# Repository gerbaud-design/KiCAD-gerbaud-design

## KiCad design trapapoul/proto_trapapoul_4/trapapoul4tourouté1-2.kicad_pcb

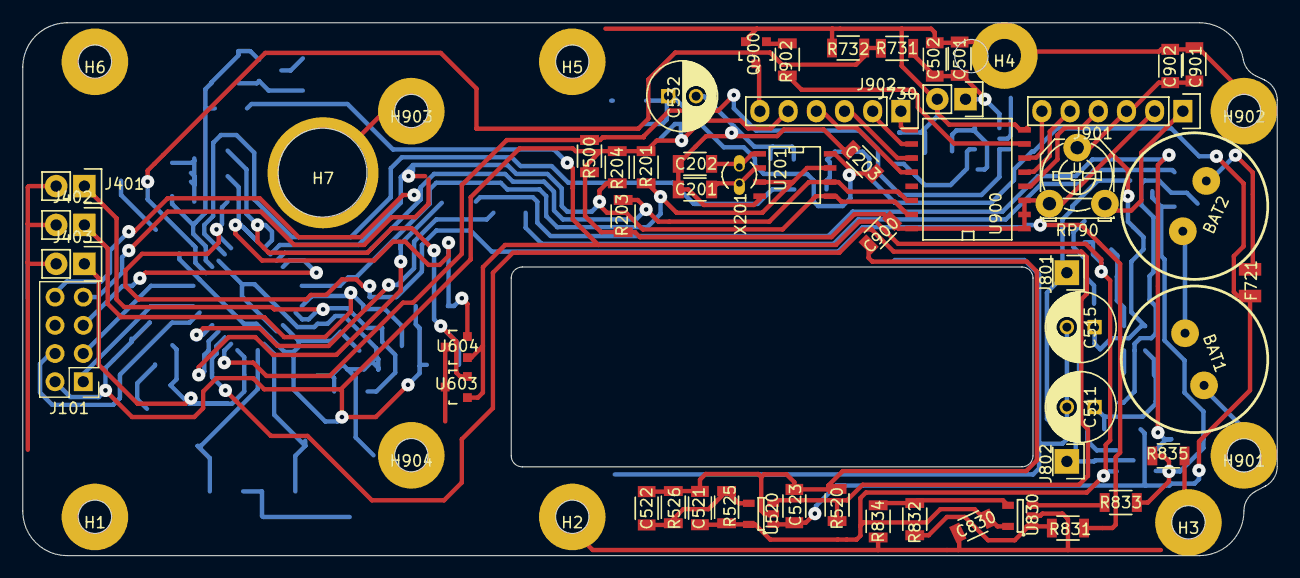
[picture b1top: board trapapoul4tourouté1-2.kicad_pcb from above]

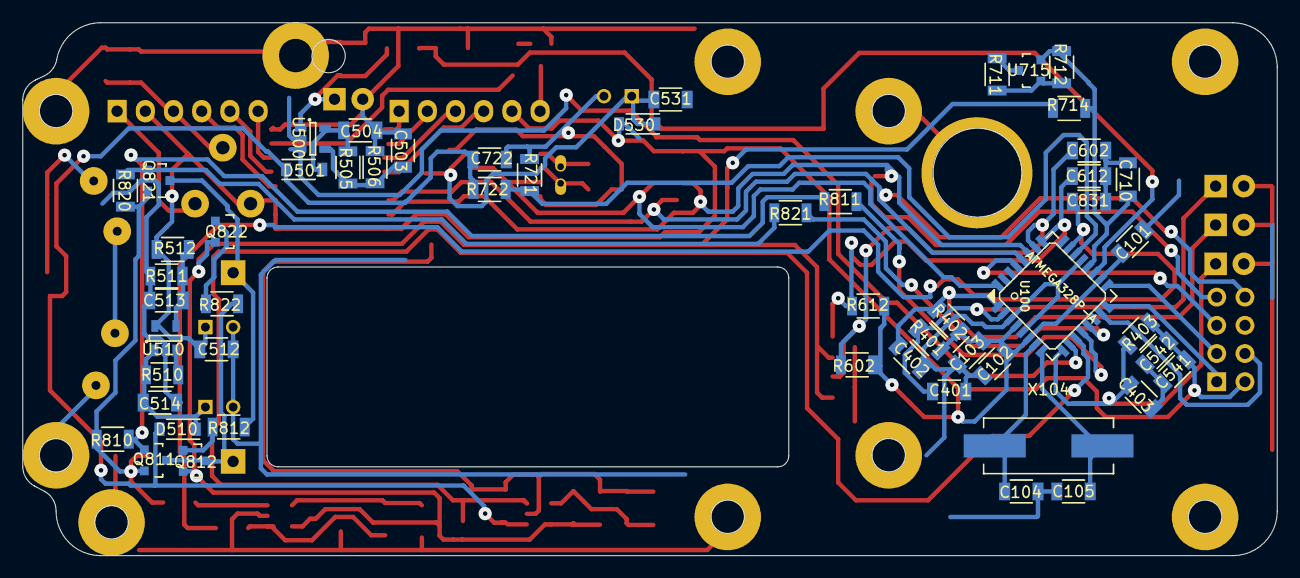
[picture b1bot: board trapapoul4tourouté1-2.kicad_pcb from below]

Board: 2 copper layers, 113.0 x 48.0 mm, 116 parts (54 on the bottom side), 60 nets.

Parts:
BAT1, BAT2: BAT; HFC1330
C101, C103, C203, C401, C402, C403, C502, C541, C710: 10n; C_1206
C102, C830, C831: 100n; C_1206
C104, C105, C201, C202: 10p; C_1206
C501, C504, C512, C514, C521, C523, C531, C722, C902: 10uF; C_1206
C503, C513, C522: 470p; C_1206
C511, C515, C532: 470uF; C_Radial_D6.3_L11.2_P2.5
C542, C602, C612, C900: 100nF; C_1206
C901: 10nF; C_1206
D501, D510, D530: SCHOTTKY; SOD-123
F721: 5A; Fuse_SMD1206_Reflow
H1, H2, H3, H4, H5, H6, H901, H902, H903, H904: hole; 3mm_screw
H7: hole; MF85
J101: HEADER_4x2; Pin_Header_Straight_2x04_Pitch2.54mm
J401, J402, J403, J730: HEADER_2; Pin_Header_Straight_1x02
J801, J802: HEADER_1; Pin_Header_Straight_1x01
J901, J902: HEADER_6; Pin_Header_Straight_1x06
Q811, Q821, Q900: PBSS4320; SOT-23
Q812, Q822: PBSS5350; SOT-23
R201, R401, R402, R403, R500, R510, R520, R711, R714, R722, R731, R832: 10k; R_1206
R203, R204, R732: 2.2k; R_1206
R505, R506, R525, R526: tbd; R_1206
R511: 100k; R_1206
R512: 33k; R_1206
R602, R612: 4k7; R_1206
R712, R721, R902: 4.7k; R_1206
R810, R820: 3k3; R_1206
R811, R812, R821, R822: 330; R_1206
R831, R833, R834: 1k; R_1206
R835: 0R2; R_1206
RP90: 100k; Potentiometer_Triwood_RM-065
U100: ATMEGA328P-A; lqfp32
U201: MCP7940; SOIC-8-N
U500, U510, U520: MIC5205; SOT-23-5
U603, U604: A3144; SOT-23
U715: TLV431-DBZ; SOT-23
U830: MCP601-SOT; SOT-23-5
U900: PCF8574; SO-16-W
X104: 16M; Crystal_HC49-SD_SMD
X201: 32.768K; Crystal_Round_Vertical_3mm_BigPad

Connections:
BP1: C401.1, J401.1, R401.2, U100.2
BP2: C402.1, J402.1, R402.2, U100.1
BP3: C403.1, J403.1, R403.2, U100.9
C_bkw: R821.1, U100.13
C_frw: R811.2, U100.12
GND: BAT1.2, C101.1, C102.1, C103.1, C104.1, C105.1, C201.2, C202.2, C203.2, C401.2, C402.2, C403.2, C501.2, C502.2, C503.2, C504.2, C511.2, C512.2, C513.2, C514.2, C515.2, C521.2, C522.2, C523.2, C531.2, C532.2, C541.2, C542.2, C602.2, C612.1, C710.2, C722.2, C830.2, C831.2, C900.2, C901.1, C902.1, H1.1, H2.1, H3.1, H4.1, H5.1, H6.1, H7.1, H901.1, H902.1, H903.1, H904.1, J101.6, J401.2, J402.2, J403.2, J730.2, J901.1, Q900.2, R506.2, R511.1, R520.1, R526.1, R711.2, R721.1, R732.2, R834.2, R835.1, RP90.3, U100.3, U100.5, U100.21, U201.4, U500.2, U510.2, U520.2, U603.3, U604.3, U715.3, U830.2, U900.8
M_bat: R721.2, R722.2, U100.22
M_imot: C831.1, R831.1, U100.23
M_sol: R731.1, R732.1, U100.19
unnamed: BAT1.1, BAT2.2
unnamed: BAT2.1, F721.1
unnamed: C104.2, U100.7, X104.1
unnamed: C105.2, U100.8, X104.2
unnamed: C201.1, U201.2, X201.2
unnamed: C202.1, U201.1, X201.1
unnamed: C503.1, R505.2, R506.1, U500.4
unnamed: C504.1, D501.2, R505.1, U500.5
unnamed: C511.1, C514.1, D510.1, R510.1, U510.1
unnamed: C513.1, R511.2, R512.1, U510.4
unnamed: C522.1, R525.1, R526.2, U520.4
unnamed: C901.2, C902.2, J901.3, RP90.2
unnamed: J101.1, U100.16
unnamed: J101.3, U100.17
unnamed: J101.4, U100.15
unnamed: J101.5, U100.29
unnamed: J801.1, Q821.3, Q822.3, R812.1
unnamed: J802.1, Q811.3, Q812.3, R822.1
unnamed: J901.4, U900.4
unnamed: J901.5, U900.5
unnamed: J901.6, U900.6
unnamed: J902.1, U900.9
unnamed: J902.2, U900.10
unnamed: J902.3, U900.11
unnamed: J902.4, U900.12
unnamed: J902.6, Q900.3
unnamed: Q811.1, R810.2, R811.1
unnamed: Q811.2, Q821.2, R810.1, R820.1, R833.2, R835.2
unnamed: Q812.1, R812.2
unnamed: Q821.1, R820.2, R821.2
unnamed: Q822.1, R822.2
unnamed: Q900.1, R902.2
unnamed: R510.2, U510.3
unnamed: R711.1, R712.2, U715.1
unnamed: R831.2, R832.1, U830.1
unnamed: R832.2, R834.1, U830.4
unnamed: R833.1, U830.3
unnamed: R902.1, U900.7
SCL: J101.8, R203.2, U100.28, U201.6, U900.14
SDA: J101.7, R204.2, U100.27, U201.5, U900.15
VCC: C101.2, C102.2, C103.2, C512.1, C515.1, C541.1, C542.1, C900.1, D530.2, J101.2, J901.2, J902.5, R201.1, R203.1, R204.1, R401.1, R402.1, R403.1, R500.1, R512.2, R602.2, R612.1, RP90.1, U100.4, U100.6, U100.18, U510.5, U900.1, U900.2, U900.3, U900.16
VPP: C521.1, C830.1, Q812.2, Q822.2, R525.2, R714.1, U520.5, U603.1, U604.1, U830.5
V_bat: C523.1, C722.1, D501.1, D510.2, F721.2, R722.1, U520.1
V_ref: C710.1, R712.1, R714.2, U100.20, U715.2
V_rtc: C203.1, C531.1, C532.1, D530.1, U201.8
V_sol: C501.1, C502.1, J730.1, R731.2, U500.1
VppEn: R520.2, U100.11, U520.3
alarm: R201.2, U100.32, U201.3, U201.7
charge_OFF: R500.2, U100.10, U500.3
quadA: C602.1, R602.1, U100.26, U603.2
quadB: C612.2, R612.2, U100.25, U604.2

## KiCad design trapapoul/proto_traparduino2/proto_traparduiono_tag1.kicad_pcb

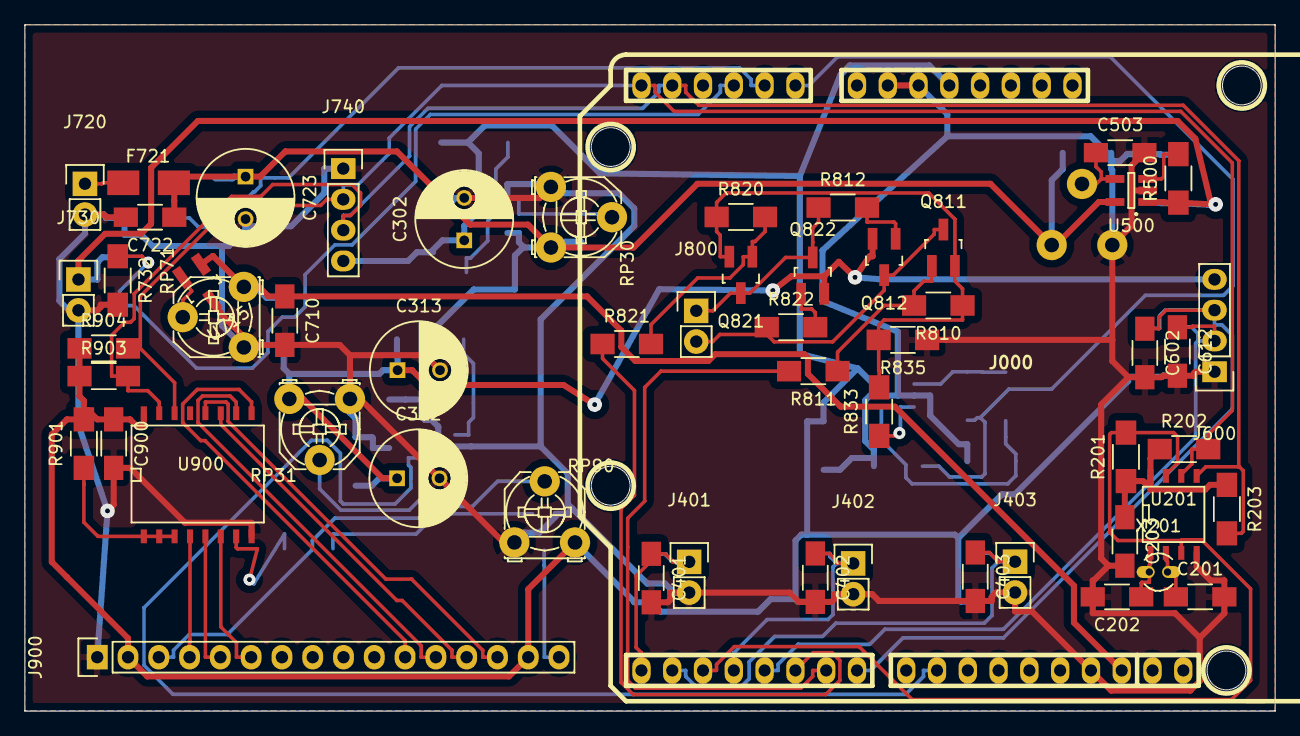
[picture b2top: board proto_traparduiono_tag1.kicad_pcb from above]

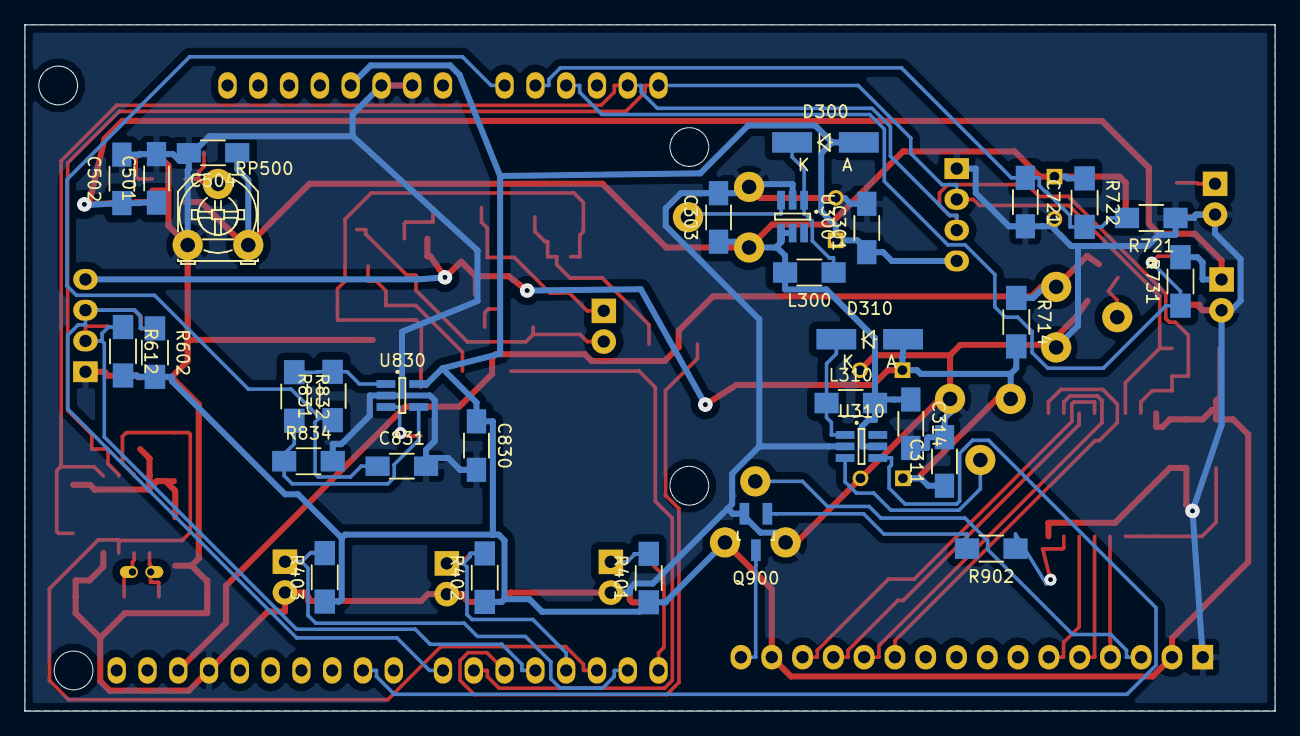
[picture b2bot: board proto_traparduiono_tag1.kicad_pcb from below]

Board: 2 copper layers, 103.1 x 56.6 mm, 88 parts (32 on the bottom side), 53 nets.

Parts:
C201, C202: 10p; C_1206_HandSoldering
C203, C401, C402, C403, C502, C503, C710, C721: 10n; C_1206_HandSoldering
C301, C303, C311, C314, C501, C504, C722: 10uF; C_1206_HandSoldering
C302, C312, C313, C723: 470uF; C_Radial_D8_L11.5_P3.5
C602, C612, C900: 100nF; C_1206_HandSoldering
C830, C831: 100n; C_1206_HandSoldering
D300, D310: SCHOTTKY; MiniMELF_Handsoldering
F721: 5A; Fuse_SMD1206_HandSoldering
J000: Arduino_Header; arduino_header
J401, J402, J403, J720, J730, J800: HEADER_2; Pin_Header_Straight_1x02
J600, J740: HEADER_4; Pin_Header_Straight_1x04
J900: HEADER_16; Pin_Header_Straight_1x16
L300, L310: INDUCTOR; R_1206_HandSoldering
Q811, Q821, Q900: PBSS4320; SOT-23_Handsoldering
Q812, Q822: PBSS5350; SOT-23_Handsoldering
R201, R401, R402, R403, R500, R714, R721, R722, R731, R732, R832, R901: 10k; R_1206_HandSoldering
R202, R203, R903, R904: 2.2k; R_1206_HandSoldering
R602, R612: 4k7; R_1206_HandSoldering
R810, R820: 3k3; R_1206_HandSoldering
R811, R812, R821, R822: 330; R_1206_HandSoldering
R831, R833, R834: 1k; R_1206_HandSoldering
R835: 0R2; R_1206_HandSoldering
R902: 4.7k; R_1206_HandSoldering
RP30, RP31, RP71, RP90, RP500: 10k; Potentiometer_Triwood_RM-065
U201: MCP7940; SOIC-8-N
U300, U310: MT3608; SOT-23-6_Handsoldering
U500: MIC5205; SOT-23-5_Handsoldering
U715: TLV431-DBZ; SOT-23_Handsoldering
U830: MCP601-SOT; SOT-23-5_Handsoldering
U900: PCF8574; SO-16-W
X201: 32.768K; Crystal_Round_Vertical_3mm_BigPad

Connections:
+12V: C311.1, C312.1, C313.1, D310.2, J600.4, Q812.2, Q822.2, R714.2, RP31.3
BP1: C401.1, J000.15, J401.1, R401.2
BP2: C402.1, J000.18, J402.1, R402.2
BP3: C403.1, J000.16, J403.1, R403.2
C_bkw: J000.20, R821.1
C_frw: J000.21, R811.2
GND: C201.2, C202.2, C203.2, C301.2, C302.2, C303.2, C311.2, C312.2, C313.2, C314.2, C401.2, C402.2, C403.2, C501.2, C502.2, C503.2, C504.2, C602.2, C612.2, C710.2, C721.2, C722.2, C723.2, C830.2, C831.2, C900.2, J000.6, J000.7, J000.29, J401.2, J402.2, J403.2, J600.1, J720.2, J730.2, J740.1, J900.1, Q900.2, R721.1, R732.2, R834.2, R835.1, RP30.1, RP31.1, RP71.1, RP90.1, RP500.1, U201.4, U300.2, U310.2, U500.2, U715.3, U830.2, U900.8
M_bat: C721.1, J000.10, R721.2, R722.2
M_imot: C831.1, J000.9, R831.1
M_sol: J000.11, R731.1, R732.1
unnamed: C201.1, U201.2, X201.2
unnamed: C202.1, U201.1, X201.1
unnamed: C503.1, RP500.2, U500.4
unnamed: D300.1, L300.1, U300.1
unnamed: D310.1, L310.1, U310.1
unnamed: F721.1, J720.1
unnamed: J900.3, RP90.2
unnamed: J900.4, U900.4
unnamed: J900.5, U900.5
unnamed: J900.6, U900.6
unnamed: J900.11, U900.9
unnamed: J900.12, U900.10
unnamed: J900.13, U900.11
unnamed: J900.14, U900.12
unnamed: J900.16, Q900.3
unnamed: Q811.1, R810.2, R811.1
unnamed: Q811.2, Q821.2, R810.1, R820.1, R833.2, R835.2
unnamed: Q812.1, R812.2
unnamed: Q821.1, R820.2, R821.2
unnamed: Q822.1, R822.2
unnamed: Q900.1, R902.2
unnamed: R500.2, U500.3
unnamed: R831.2, R832.1, U830.1
unnamed: R832.2, R834.1, U830.4
unnamed: R833.1, U830.3
unnamed: R901.1, U900.1, U900.2, U900.3
unnamed: R902.1, U900.7
unnamed: RP30.2, U300.3
unnamed: RP31.2, U310.3
unnamed: RP71.2, U715.2
SCL: J000.14, J740.2, R202.2, R904.2, U201.6, U900.14
SDA: J000.13, J740.3, R203.2, R903.2, U201.5, U900.15
VCC: C301.1, C302.1, C830.1, C900.1, D300.2, J000.5, J740.4, J900.2, J900.15, R401.1, R402.1, R403.1, R602.2, R612.2, R901.2, R903.1, R904.1, RP90.3, U830.5, U900.16
V_bat: C303.1, C314.1, C504.1, C722.1, C723.1, F721.2, L300.2, L310.2, R722.1, RP30.3, RP500.3, U300.4, U300.5, U310.5, U500.5
V_ref: C710.1, J000.30, R714.1, RP71.3, U715.1
V_rtc: C203.1, R201.1, R202.1, R203.1, U201.8
V_sol: C501.1, C502.1, J730.1, R500.1, R731.2, U500.1
alarm: J000.17, R201.2, U201.3, U201.7
buzz: J000.24, U310.4
mot_A: J800.1, Q821.3, Q822.3, R812.1
mot_B: J800.2, Q811.3, Q812.3, R822.1
quadA: C602.1, J000.22, J600.3, R602.1
quadB: C612.1, J000.19, J600.2, R612.1
